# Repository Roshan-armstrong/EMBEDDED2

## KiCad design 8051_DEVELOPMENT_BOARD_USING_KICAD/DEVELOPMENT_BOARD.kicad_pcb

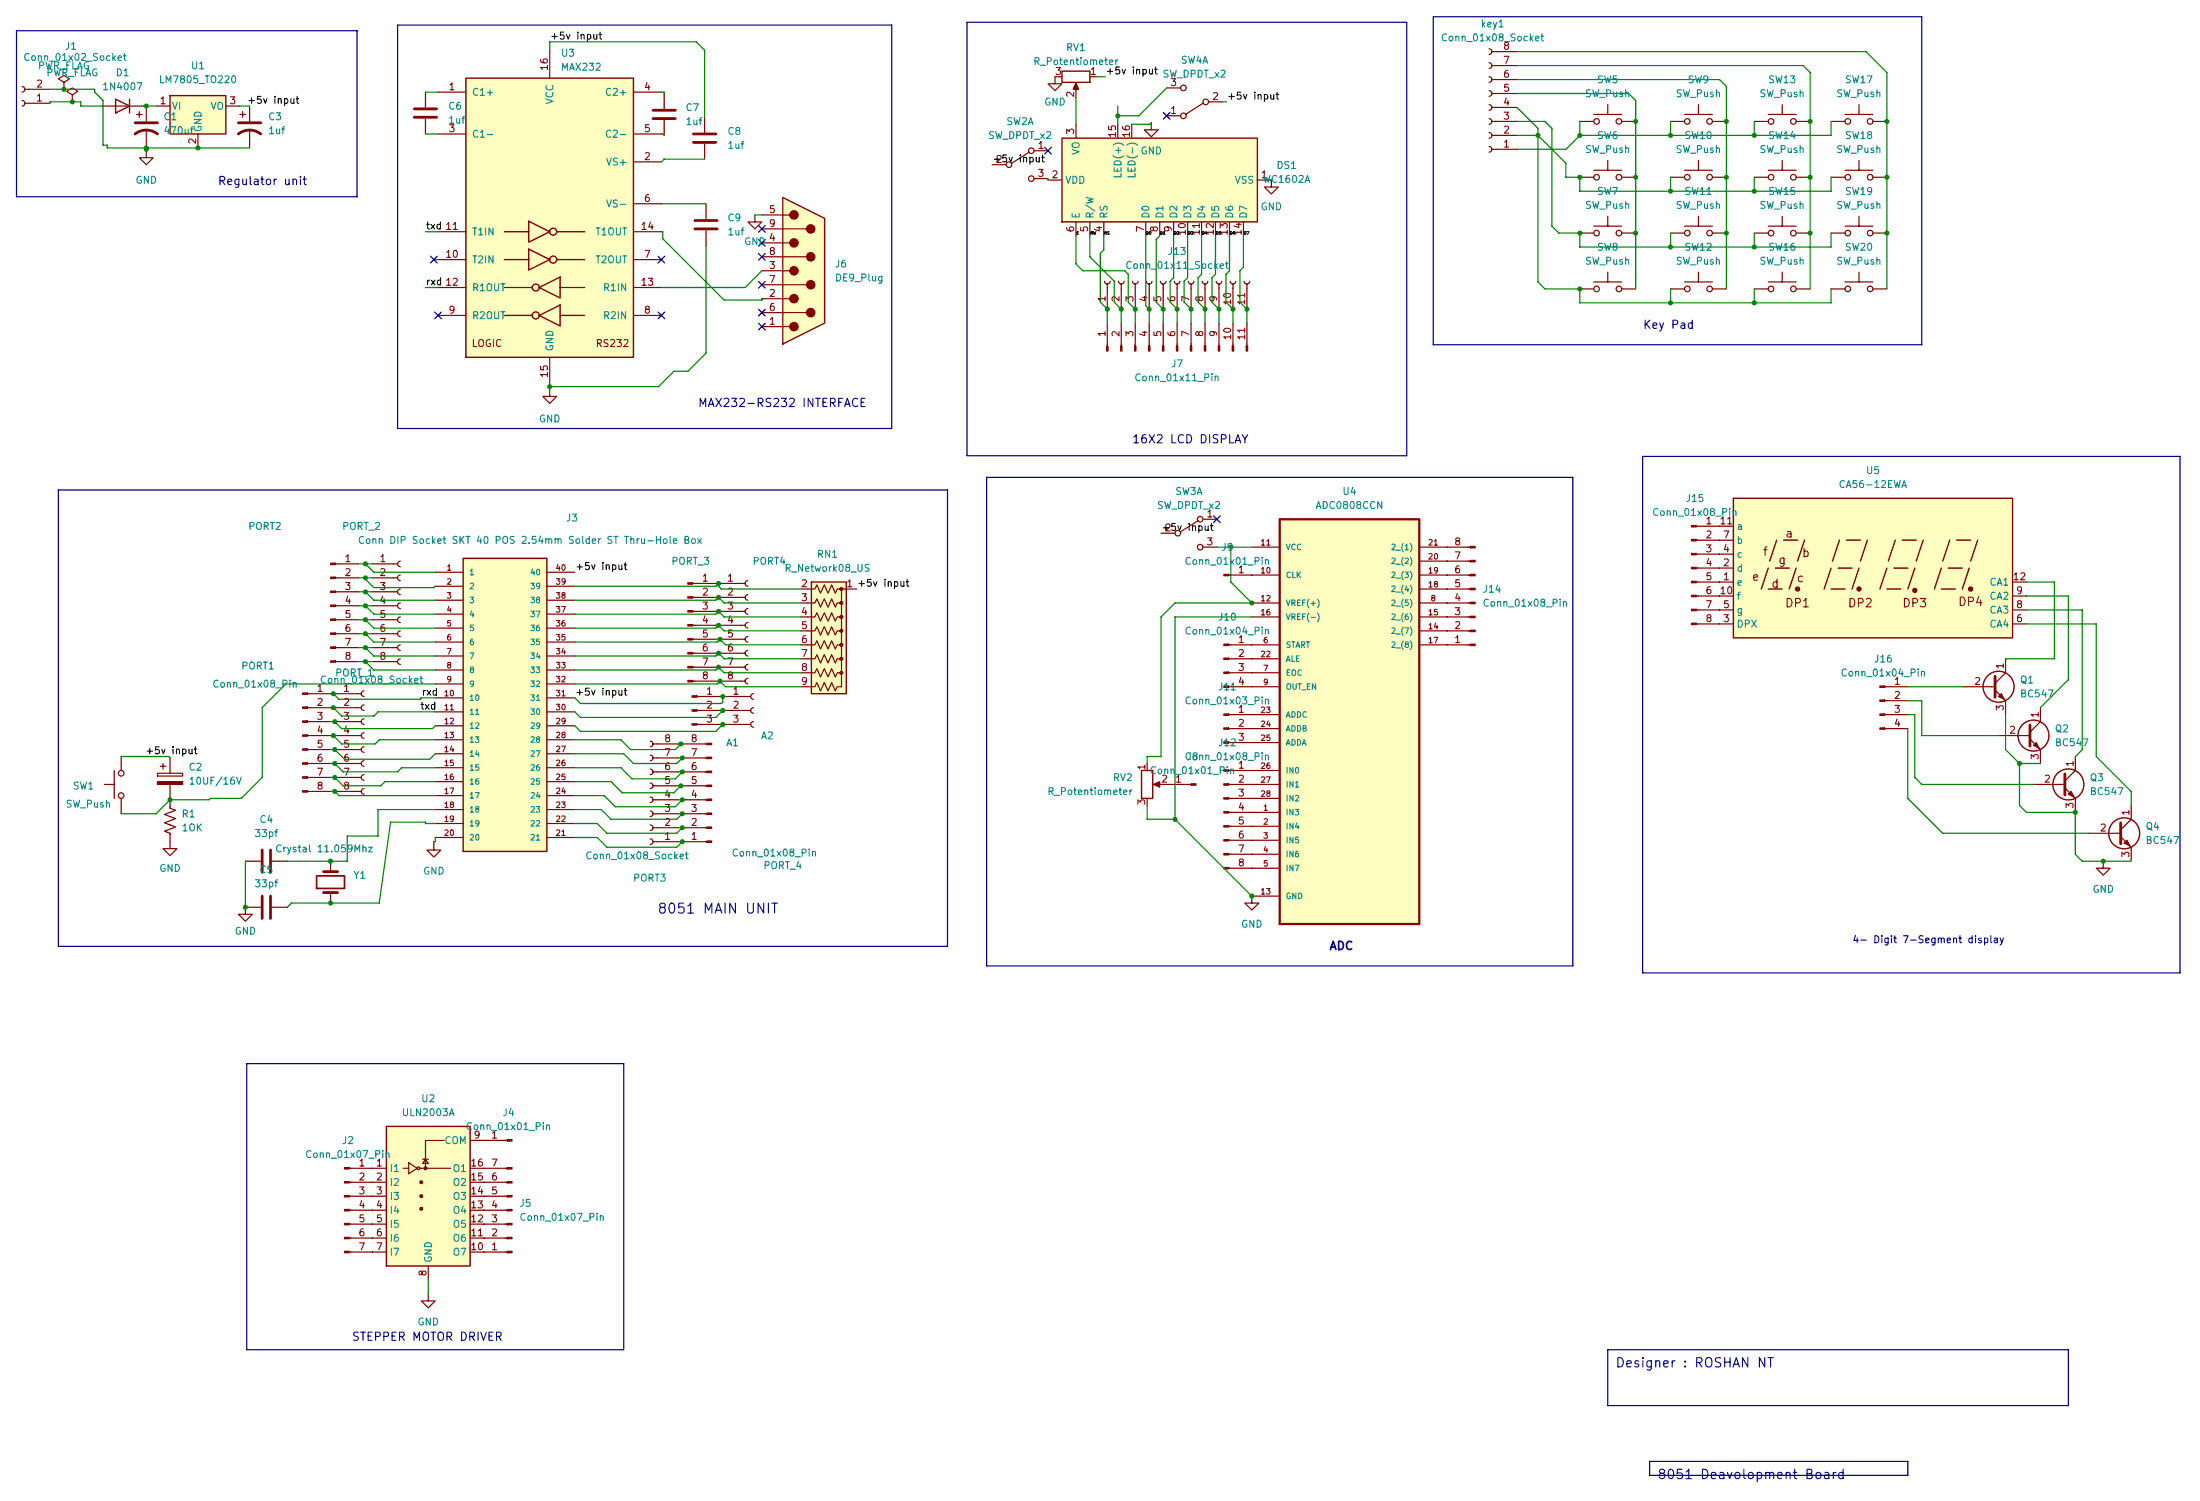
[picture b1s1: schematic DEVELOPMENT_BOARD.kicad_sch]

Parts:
A1: Conn_01x03_Pin; PinHeader_1x03_P2.54mm_Vertical
A2: Conn_01x03_Socket; PinSocket_1x03_P2.54mm_Vertical
C1: 470uf; C_Radial_D8.0mm_H7.0mm_P3.50mm
C2: 10UF/16V; C_Radial_D5.0mm_H11.0mm_P2.00mm
C3, C6, C7, C8, C9: 1uf; C_Disc_D5.0mm_W2.5mm_P5.00mm
C4, C5: 33pf; C_Disc_D5.0mm_W2.5mm_P5.00mm
D1: 1N4007; D_DO-41_SOD81_P10.16mm_Horizontal
DS1: WC1602A
J1: Conn_01x02_Socket; PinSocket_1x02_P2.54mm_Vertical
J2, J5: Conn_01x07_Pin; PinHeader_1x07_P2.54mm_Vertical
J3: Conn DIP Socket SKT 40 POS 2.54mm Solder ST Thru-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; Dip_zif_40
J4, J8, J9: Conn_01x01_Pin; PinHeader_1x01_P2.54mm_Vertical
J6: DE9_Plug; DSUB-9_Male_Horizontal_P2.77x2.54mm_EdgePinOffset9.40mm
J7: Conn_01x11_Pin; PinHeader_1x11_P2.54mm_Vertical
J10, J16: Conn_01x04_Pin; PinHeader_1x04_P2.54mm_Vertical
J11: Conn_01x03_Pin; PinHeader_1x03_P2.54mm_Vertical
J12, J14, J15: Conn_01x08_Pin; PinHeader_1x08_P2.54mm_Vertical
J13: Conn_01x11_Socket; PinSocket_1x11_P2.54mm_Vertical
PORT1, PORT2: Conn_01x08_Pin; PinHeader_1x08_P2.54mm_Vertical
PORT3, PORT4: Conn_01x08_Socket; PinSocket_1x08_P2.54mm_Vertical
PORT_1, PORT_2: Conn_01x08_Socket; PinSocket_1x08_P2.54mm_Vertical
PORT_3, PORT_4: Conn_01x08_Pin; PinHeader_1x08_P2.54mm_Vertical
Q1, Q2, Q3, Q4: BC547; TO-92_Inline
R1: 1OK; R_Axial_DIN0414_L11.9mm_D4.5mm_P5.08mm_Vertical
RN1: R_Network08_US; R_Array_SIP9
RV1, RV2: R_Potentiometer; Potentiometer_Runtron_RM-065_Vertical
SW1: SW_Push; SW_PUSH_6mm_H4.3mm
SW2, SW3, SW4: SW_DPDT_x2; SW_CuK_JS202011CQN_DPDT_Straight
SW5, SW6, SW7, SW8, SW9, SW10, SW11, SW12, SW13, SW14, SW15, SW16, SW17, SW18, SW19, SW20: SW_Push; SW_Tactile_Straight_KSL0Axx1LFTR
U1: LM7805_TO220; TO-220-3_Vertical
U2: ULN2003A; DIP-16_W7.62mm_Socket
U3: MAX232; DIP-16_W10.16mm_LongPads
U4: ADC0808CCN; DIP-28_W7.62mm_Socket
U5: CA56-12EWA
Y1: Crystal 11.059Mhz; oscillator_dip_2
key1: Conn_01x08_Socket; PinSocket_1x08_P2.54mm_Vertical

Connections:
/+5v input: A1.1, A2.1, C2.1, C3.1, C8.1, J3.31, J3.40, RN1.1 (common), RV1.1, SW1.2, SW2.2 (B), SW3.2 (B), SW4.2 (B), U1.3 (VO), U3.16 (VCC)
/D0: DS1.7 (D0), J7.4, J13.4
/D1: DS1.8 (D1), J7.5, J13.5
/D2: DS1.9 (D2), J7.6, J13.6
/D3: DS1.10 (D3), J7.7, J13.7
/D4: DS1.11 (D4), J7.8, J13.8
/D5: DS1.12 (D5), J7.9, J13.9
/D6: DS1.13 (D6), J7.10, J13.10
/D7: DS1.14 (D7), J7.11, J13.11
/E: DS1.6 (E), J7.3, J13.3
/RS: DS1.4 (RS), J7.1, J13.1
/RW: DS1.5 (R/W), J7.2, J13.2
/rxd: J3.10, PORT1.1, PORT_1.1, U3.12 (R1OUT)
/txd: J3.11, PORT1.2, PORT_1.2, U3.11 (T1IN)
GND: C1.2, C3.2, C4.1, C5.1, C9.2, DS1.1 (VSS), DS1.16 (LED(-)), J1.2, J3.20, J6.5, Q1.3 (E), Q2.3 (E), Q3.3 (E), Q4.3 (E), R1.2, RV1.3, RV2.3, U1.2 (GND), U2.8 (GND), U3.15 (GND), U4.13 (GND), U4.16 (VREF(-))
unnamed: A1.2, A2.2, J3.30
unnamed: A1.3, A2.3, J3.29
unnamed: C2.2, J3.9, R1.1, SW1.1
unnamed: C4.2, J3.18, Y1.2
unnamed: C5.2, J3.19, Y1.1
unnamed: D1.2 (A), J1.1
unnamed: C1.1, D1.1 (K), U1.1 (VI)
unnamed: DS1.15 (LED(+)), SW4.3 (C)
unnamed: DS1.2 (VDD), SW2.3 (C)
unnamed: DS1.3 (VO), RV1.2
unnamed: J2.1, U2.1 (I1)
unnamed: J2.2, U2.2 (I2)
unnamed: J2.3, U2.3 (I3)
unnamed: J2.4, U2.4 (I4)
unnamed: J2.5, U2.5 (I5)
unnamed: J2.6, U2.6 (I6)
unnamed: J2.7, U2.7 (I7)
unnamed: J4.1, U2.9 (COM)
unnamed: J5.1, U2.10 (O7)
unnamed: J5.2, U2.11 (O6)
unnamed: J5.3, U2.12 (O5)
unnamed: J5.4, U2.13 (O4)
unnamed: J5.5, U2.14 (O3)
unnamed: J5.6, U2.15 (O2)
unnamed: J5.7, U2.16 (O1)
unnamed: J8.1, RV2.2
unnamed: J9.1, U4.10 (CLK)
unnamed: J10.1, U4.6 (START)
unnamed: J10.2, U4.22 (ALE)
unnamed: J10.3, U4.7 (EOC)
unnamed: J10.4, U4.9 (OUT_EN)
unnamed: J11.1, U4.23 (ADDC)
unnamed: J11.2, U4.24 (ADDB)
unnamed: J11.3, U4.25 (ADDA)
unnamed: J12.1, U4.26 (IN0)
unnamed: J12.2, U4.27 (IN1)
unnamed: J12.3, U4.28 (IN2)
unnamed: J12.4, U4.1 (IN3)
unnamed: J12.5, U4.2 (IN4)
unnamed: J12.6, U4.3 (IN5)
unnamed: J12.7, U4.4 (IN6)
unnamed: J12.8, U4.5 (IN7)
unnamed: J14.1, U4.17 (2_(8))
unnamed: J14.2, U4.14 (2_(7))
unnamed: J14.3, U4.15 (2_(6))
unnamed: J14.4, U4.8 (2_(5))
unnamed: J14.5, U4.18 (2_(4))
unnamed: J14.6, U4.19 (2_(3))
unnamed: J14.7, U4.20 (2_(2))
unnamed: J14.8, U4.21 (2_(1))
unnamed: J15.1, U5.11 (a)
unnamed: J15.2, U5.7 (b)
unnamed: J15.3, U5.4 (c)
unnamed: J15.4, U5.2 (d)
unnamed: J15.5, U5.1 (e)
unnamed: J15.6, U5.10 (f)
unnamed: J15.7, U5.5 (g)
unnamed: J15.8, U5.3 (DPX)
unnamed: J16.1, Q1.2 (B)
unnamed: J16.2, Q2.2 (B)
unnamed: J16.3, Q3.2 (B)
unnamed: J16.4, Q4.2 (B)
unnamed: J3.12, PORT1.3, PORT_1.3
unnamed: J3.13, PORT1.4, PORT_1.4
unnamed: J3.14, PORT1.5, PORT_1.5
unnamed: J3.15, PORT1.6, PORT_1.6
unnamed: J3.16, PORT1.7, PORT_1.7
unnamed: J3.17, PORT1.8, PORT_1.8
unnamed: J3.1, PORT2.1, PORT_2.1
unnamed: J3.2, PORT2.2, PORT_2.2
unnamed: J3.3, PORT2.3, PORT_2.3
unnamed: J3.4, PORT2.4, PORT_2.4
unnamed: J3.5, PORT2.5, PORT_2.5
unnamed: J3.6, PORT2.6, PORT_2.6
unnamed: J3.7, PORT2.7, PORT_2.7
unnamed: J3.8, PORT2.8, PORT_2.8
unnamed: J3.21, PORT3.1, PORT_4.1
unnamed: J3.22, PORT3.2, PORT_4.2
unnamed: J3.23, PORT3.3, PORT_4.3
unnamed: J3.24, PORT3.4, PORT_4.4
unnamed: J3.25, PORT3.5, PORT_4.5
unnamed: J3.26, PORT3.6, PORT_4.6
unnamed: J3.27, PORT3.7, PORT_4.7
unnamed: J3.28, PORT3.8, PORT_4.8
unnamed: J3.39, PORT4.1, PORT_3.1, RN1.2 (R1)
unnamed: J3.38, PORT4.2, PORT_3.2, RN1.3 (R2)
unnamed: J3.37, PORT4.3, PORT_3.3, RN1.4 (R3)
unnamed: J3.36, PORT4.4, PORT_3.4, RN1.5 (R4)
unnamed: J3.35, PORT4.5, PORT_3.5, RN1.6 (R5)
unnamed: J3.34, PORT4.6, PORT_3.6, RN1.7 (R6)
unnamed: J3.33, PORT4.7, PORT_3.7, RN1.8 (R7)
unnamed: J3.32, PORT4.8, PORT_3.8, RN1.9 (R8)
unnamed: Q1.1 (C), U5.12 (CA1)
unnamed: Q2.1 (C), U5.9 (CA2)
unnamed: Q3.1 (C), U5.8 (CA3)
unnamed: Q4.1 (C), U5.6 (CA4)
unnamed: RV2.1, SW3.3 (C), U4.11 (VCC), U4.12 (VREF(+))
unnamed: C6.1, U3.1 (C1+)
unnamed: C6.2, U3.3 (C1-)
unnamed: C7.1, U3.4 (C2+)
unnamed: C7.2, U3.5 (C2-)
unnamed: J6.3, U3.13 (R1IN)
unnamed: J6.2, U3.14 (T1OUT)
unnamed: C8.2, U3.2 (VS+)
unnamed: C9.1, U3.6 (VS-)
unnamed: SW5.1, SW9.1, SW13.1, SW17.1, key1.1
unnamed: SW6.1, SW8.1, SW10.1, SW12.1, SW14.1, SW16.1, SW18.1, SW20.1, key1.2, key1.4
unnamed: SW7.1, SW11.1, SW15.1, SW19.1, key1.3
unnamed: SW5.2, SW6.2, SW7.2, SW8.2, key1.5
unnamed: SW9.2, SW10.2, SW11.2, SW12.2, key1.6
unnamed: SW13.2, SW14.2, SW15.2, SW16.2, key1.7
unnamed: SW17.2, SW18.2, SW19.2, SW20.2, key1.8

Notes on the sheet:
Designer : ROSHAN NT
8051 Deavolopment Board
MAX232-RS232 INTERFACE
STEPPER MOTOR DRIVER
ADC
4- Digit 7-Segment display
8051 MAIN UNIT
Key Pad
16X2 LCD DISPLAY
Regulator unit

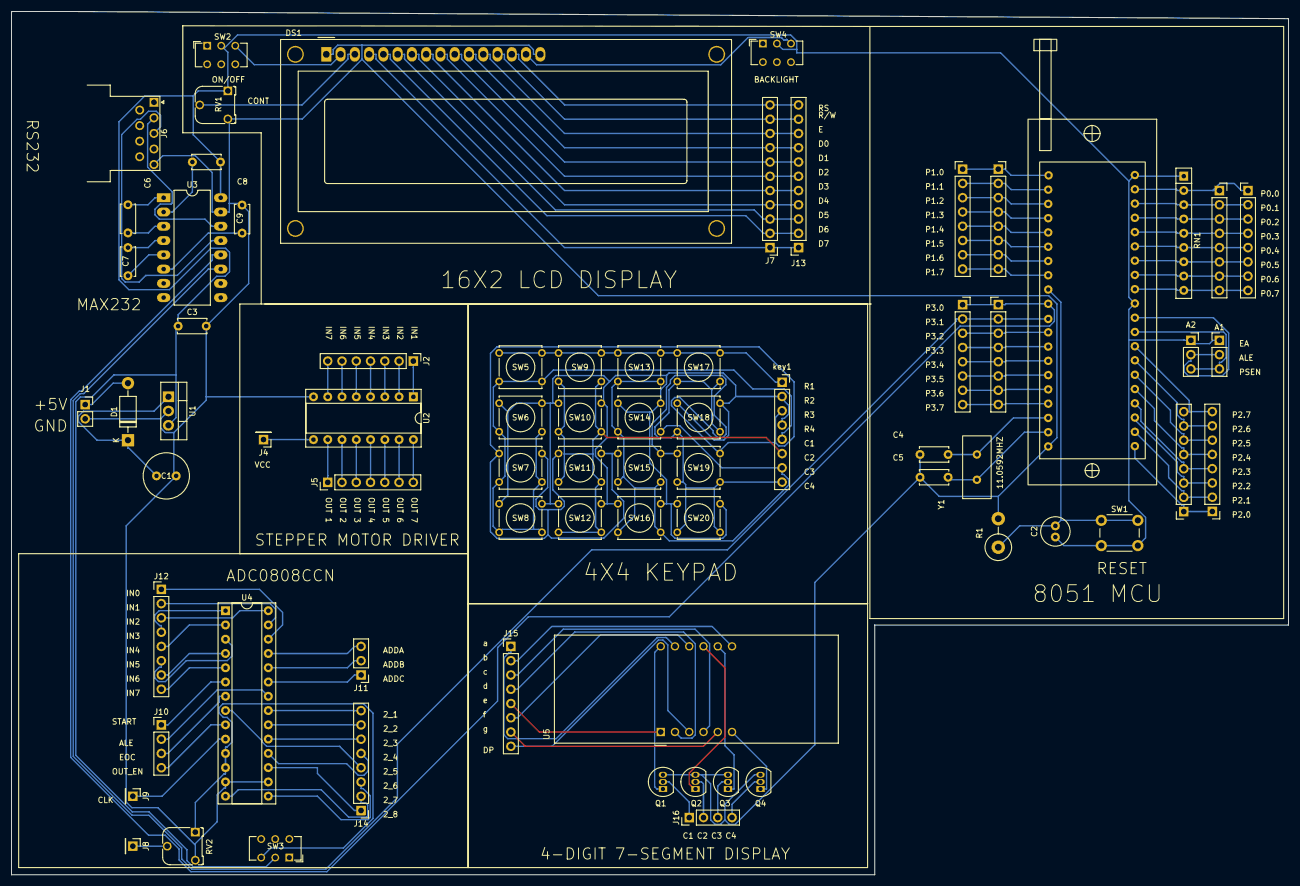
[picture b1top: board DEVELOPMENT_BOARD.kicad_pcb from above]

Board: 2 copper layers, 227.3 x 153.7 mm, 72 parts (0 on the bottom side), 127 nets.

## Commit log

2023-09-09 project folder
